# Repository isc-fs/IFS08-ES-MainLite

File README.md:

# IFS08-ES-MainLite

Hardware design, KiCad schematic and PCB layout of the **MainLite**, the minimal STM32H733ZG control module of the **IFS08**, developed for the **ISC Formula Student Racing Team** (Season 2025/2026). Mounted on a backplane, the same module becomes the **AMS**, the **ECU** or the **uDV**.

[-green.svg)]()
[-red.svg)]()

---

## Getting started

1. Create a GitHub account if you don't have one yet.
2. Download and install [GitHub Desktop](https://desktop.github.com/) (beginner) or [Git CLI](https://git-scm.com/book/en/v2/Getting-Started-Installing-Git) (advanced).
   - If this is your first time using GitHub Desktop, make sure to read the [User Manual](https://help.github.com/desktop/guides/).
   - If this is your first time using Git, start with a tutorial:
     - [Git Tutorial](https://git-scm.com/docs/gittutorial)
     - [Atlassian Git Tutorial](https://www.atlassian.com/git/tutorials/)
   - Keep a copy of [GitHub's Git Cheat Sheet](https://services.github.com/kit/downloads/github-git-cheat-sheet.pdf) handy as a reference.

3. Clone this repository to your machine:
   - **SSH:** `git@github.com:isc-fs/IFS08-ES-MainLite.git`
   - **HTTPS:** `https://github.com/isc-fs/IFS08-ES-MainLite.git`

4. Open `IFS08-MainLite/MAIN_LITE.kicad_pro` with KiCad 9.x.

---

## How we work with this repository

### Main branches

The repository follows standard ISC branching rules:

* **`main`** is the production branch. It contains only validated hardware releases, schematics, and documentation ready for track operations. Never work directly on it.
* **`dev`** (or active feature branches) is the development and integration point. Never commit directly to `main` — all changes arrive through a reviewed Pull Request.

```
main  ──────────────────●──────────────────────●──▶  (validated releases only)
                        ↑                      ↑
dev   ──────●───●───●───●───●───●───●───●───●──●──▶  (continuous integration)
            ↑   ↑       ↑   ↑   ↑       ↑   ↑
          feat/1 fix/1 feat/2 fix/2   feat/3 fix/3
```

### Feature branches

All work — whether a new hardware revision, firmware update, or bug fix — is done on a **feature branch** created from `dev` (or `main`). When the work is ready, a Pull Request is opened, reviewed, merged, and the branch is deleted.

```
feat/<n>   →  new functionality / hardware addition (feat/1, feat/2, feat/3 ...)
fix/<n>    →  bug fix / schematic correction       (fix/1,  fix/2,  fix/3  ...)
```

### Step-by-step workflow

1. **Create the branch:**
   ```bash
   git checkout dev
   git pull origin dev
   git checkout -b feat/your-feature-name
   ```
2. **Work and commit:**
   ```bash
   git add .
   git commit -m "feat(hw): add reverse polarity protection to 5V input"
   ```
3. **Push and open Pull Request:**
   ```bash
   git push origin feat/your-feature-name
   ```
   Open a PR against `dev`, verify 0 KiCad DRC/ERC errors, provide test evidence, and request review from the Electronics Subsystem Technical Director.

---

## 1. Project Overview & System Purpose

The **MainLite** is a small, self-contained STM32H733ZG module: MCU, 3.3 V regulation, three CAN transceivers, IMU, microSD, USB-C and SWD. Everything that changes between car subsystems lives on the **backplane** it plugs into through two 1×18 2.54 mm headers (**J3** and **J4**):

| Role | Node id (CAN bootloader) | Flash bus |
| :--- | :---: | :---: |
| **ECU** — vehicle control unit | `0x1` | FDCAN2 |
| **AMS** — accumulator management system | `0x2` | FDCAN1 |
| **uDV** — driverless interface | `0x3` | FDCAN2 |

Every MainLite carries the ISC CAN bootloader in flash sector 0.

```
                 +--------------------------------------------------------------+
   USB-C (J5) ---+  ESD (D3/D4)   +5V <- VBUS (D11)        SWD (J2: GND/CLK/DIO/VDD)
                 |                                                              |
   +5V (J4.17/18)+--> LD39200 (U1) --> VDD 3.3 V --> J4.15/16                   |
                 |                                                              |
                 |      +--------------------------------------------+         |
                 |      |        STM32H733ZGTx (U5, LQFP-144)         |         |
                 |      |  HSE 24 MHz (Y1)                            |         |
                 |      +--+---------+---------+---------+------+----+         |
                 |         |FDCAN1   |FDCAN2   |FDCAN3   |I2C2  |SDMMC1        |
                 |      TCAN330   TCAN330   TCAN330   BMI088  microSD (J1)      |
                 |       (U2)      (U3)      (U4)     (IC1)    4-bit, CD PE3    |
                 |      120R R1   120R R5   120R R9                             |
                 +--------+---------+---------+-----------------------------+---+
                          |         |         |                             |
                   J4.3/4 CAN1  J4.5/6 CAN2  J4.7/8 CAN3     J3: 13 GPIO, USART10, 1-Wire
                                                            J4: SPI1 + nRF24 CS/CE/IRQ
```

---

## 2. Hardware Architecture & Electrical Specifications

| Block | Part | Notes |
| :--- | :--- | :--- |
| MCU | STM32H733ZGTx (U5) | Cortex-M7 @ 550 MHz, 1 MB flash, LQFP-144 |
| Clock | 24 MHz crystal (Y1) | HSE on PH0/PH1, 10 pF load caps (C5/C6) |
| 3.3 V rail | ST LD39200PU33R (U1) | From `+5V` (backplane J4.17/18 or USB VBUS through D11) |
| CAN | 3× TI TCAN330 (U2/U3/U4) | FDCAN1 PD0/PD1, FDCAN2 PB12/PB13, FDCAN3 PG10/PG9; fixed 120 Ω terminations R1/R5/R9 |
| IMU | Bosch BMI088 (IC1) | I2C2 PF0/PF1, accel `0x18`, gyro `0x68`, no external pull-ups |
| Storage | microSD (J1, Molex 104031-0811) | SDMMC1 4-bit PC8–PC12/PD2, 33 Ω series, 47 kΩ pull-ups, card detect PE3 |
| USB | USB-C (J5, GCT USB4085) | USB_OTG_HS FS PHY PA11/PA12, VBUS sense PA9 (100k/47k) |
| Debug | 1×4 header (J2) | GND, SWCLK (PA14), SWDIO (PA13), VDD |
| Status | 2× LED | `OK_STATUS` PD14, `ERR_STATUS` PD15 |
| Buttons | SW1 / SW2 | BOOT0, NRST |
| VBAT | — | Not connected (no backup battery) |

---

## 3. Backplane Connectors (J3 / J4)

| Pin | J3 net | J3 MCU | J4 net | J4 MCU / part |
| :---: | :--- | :--- | :--- | :--- |
| 1 | `GND` | — | `GND` | — |
| 2 | `GND` | — | `GND` | — |
| 3 | `DS18B20_REFRI` | PD5 (pin 119) | `CANL1` | R1.2, U2.6 |
| 4 | `USART10_RX` | PG11 (pin 126) | `CANH1` | R1.1, U2.7 |
| 5 | `USART10_TX` | PG12 (pin 127) | `CANH2` | R5.1, U3.7 |
| 6 | `GPIO1` | PB4 (pin 134) | `CANL2` | R5.2, U3.6 |
| 7 | `GPIO2` | PB5 (pin 135) | `CANH3` | R9.1, U4.7 |
| 8 | `GPIO3` | PB6 (pin 136) | `CANL3` | R9.2, U4.6 |
| 9 | `GPIO4` | PB7 (pin 137) | `NRF24_CS` | PB0 (pin 46) |
| 10 | `GPIO5` | PB8 (pin 139) | `NRF24_CE` | PC5 (pin 45) |
| 11 | `GPIO6` | PB9 (pin 140) | `NRF24_IRQ` | PC4 (pin 44) |
| 12 | `GPIO7` | PF7 (pin 19) | `SPI1_MOSI` | PA7 (pin 43) |
| 13 | `GPIO8` | PF8 (pin 20) | `SPI1_MISO` | PA6 (pin 42) |
| 14 | `GPIO9` | PF9 (pin 21) | `SPI1_SCK` | PA5 (pin 41) |
| 15 | `GPIO10` | PF10 (pin 22) | `VDD` | — |
| 16 | `GPIO11` | PC0 (pin 26) | `VDD` | — |
| 17 | `GPIO12` | PC1 (pin 27) | `+5V` | — |
| 18 | `GPIO13` | PC2_C (pin 28) | `+5V` | — |

Per-role use of these pins (which GPIO is which signal on the AMS, ECU or uDV backplane) is defined by each backplane design.

---

## 4. Machine-Readable Pin Model

[`model/mainlite.pins.yaml`](model/mainlite.pins.yaml) (JSON twin: [`mainlite.pins.json`](model/mainlite.pins.json)) lists all 144 pins of U5: net, alternate function, whether and where each one leaves the module on J3/J4, and what it connects to on the board. It also describes the CAN, SDMMC, I2C, HSE, VBAT, SWD and USB interfaces. `tools/gen_pins.py` generates it from the schematic; CI fails a PR whose committed model is stale or whose schematic has KiCad ERC errors. Each change that reaches `main` is published as a `pin-model-vX.Y` release, so other repos (e.g. the virtual HIL) can check their pin definitions against a pinned version.

```bash
python3 tools/gen_pins.py        # after any schematic change; commit model/
```

Format, versioning and how to consume it: [docs/pin-model.md](docs/pin-model.md).

---

## 5. Formal Design Documents & Reports

| Document | File Link | Description | Status |
| :--- | :--- | :--- | :--- |
| **Work Order (PDF)** | [📄 WO_ES-IFS08-MainLite.pdf](WO_ES-IFS08-MainLite.pdf) | Formal Work Order (`WO-IFS08-MLITE-001`): requirements, interfaces, verification protocol and QA sign-off sheet. | **Rev 1.0** |
| **Work Order (DOCX)** | [📄 WO_ES-IFS08-MainLite.docx](WO_ES-IFS08-MainLite.docx) | Word source of the Work Order, on the ISC base template styles. | **Rev 1.0** |
| **Markdown Specification** | [📄 WORK_ORDER_MAIN_LITE.md](docs/WORK_ORDER_MAIN_LITE.md) | Synchronized Markdown version of the Work Order for Git version control and quick online reference. | **Rev 1.0** |
| **Schematic (PDF)** | [📄 MAIN_LITE_schematic.pdf](docs/MAIN_LITE_schematic.pdf) | Eeschema PDF export of the schematic. | **v1.1** |
| **Interactive BOM** | [📄 MAIN_LITE_v1-1_BOM.html](docs/bom/MAIN_LITE_v1-1_BOM.html) | InteractiveHtmlBom export for assembly. | **v1.1** |
| **Pin model** | [📄 pin-model.md](docs/pin-model.md) | Format and use of the generated pin model. | **Schema v1** |
| **Fabrication outputs** | [📁 production/](IFS08-MainLite/production) | Gerbers/drill (`MAIN_LITE.zip`), BOM, CPL and IPC netlist as sent to fab. | **v1.1** |

---

## 6. Repository Structure

```
IFS08-ES-MainLite/
├── .github/workflows/                 # CI: pin-model check + ERC, model release on main
├── docs/                              # Documentation
│   ├── bom/
│   │   └── MAIN_LITE_v1-1_BOM.html    # Interactive BOM
│   ├── MAIN_LITE_schematic.pdf        # Schematic PDF export
│   ├── pin-model.md                   # Pin model format & usage
│   └── WORK_ORDER_MAIN_LITE.md        # Synchronized Markdown Work Order
├── IFS08-MainLite/                    # KiCad Project Files (KiCad 9.x)
│   ├── Libraries/                     # Local symbols & footprints (BMI088, LD39200, LSM115J, switch, ISC logo, MainLite module)
│   ├── production/                    # Fabrication outputs (Gerbers, BOM, CPL)
│   ├── fp-lib-table                   # Footprint Library Table
│   ├── sym-lib-table                  # Symbol Library Table
│   ├── MAIN_LITE.kicad_pro            # KiCad Project File
│   ├── MAIN_LITE.kicad_sch            # Schematic
│   └── MAIN_LITE.kicad_pcb            # PCB Layout
├── model/                             # GENERATED pin model (mainlite.pins.yaml / .json)
├── tests/                             # Pin model invariants (unittest)
├── tools/                             # gen_pins.py, kicad_export.sh, erc_summary.py, ST pin data
├── WO_ES-IFS08-MainLite.pdf           # Official Work Order (PDF)
├── WO_ES-IFS08-MainLite.docx          # Official Work Order (Word)
├── .gitignore                         # KiCad and OS Ignore Rules
└── README.md                          # Repository Documentation
```

`Libraries/MAIN_LITE/` holds the MainLite module symbol and footprint that backplane designs place to mate with J3/J4.

---

## 7. Author & Team Credits

* **Subsystem:** Low Voltage & Electronics Subsystem (ES)
* **Author & Technical Lead:** Raúl Morán
* **Team:** [ISC Formula Student Racing Team](https://www.comillas.edu/) — Universidad Pontificia Comillas (ICAI)
* **Season:** 2025 / 2026

---

*ISC Racing Team — IFS08 Electronics Subsystem*

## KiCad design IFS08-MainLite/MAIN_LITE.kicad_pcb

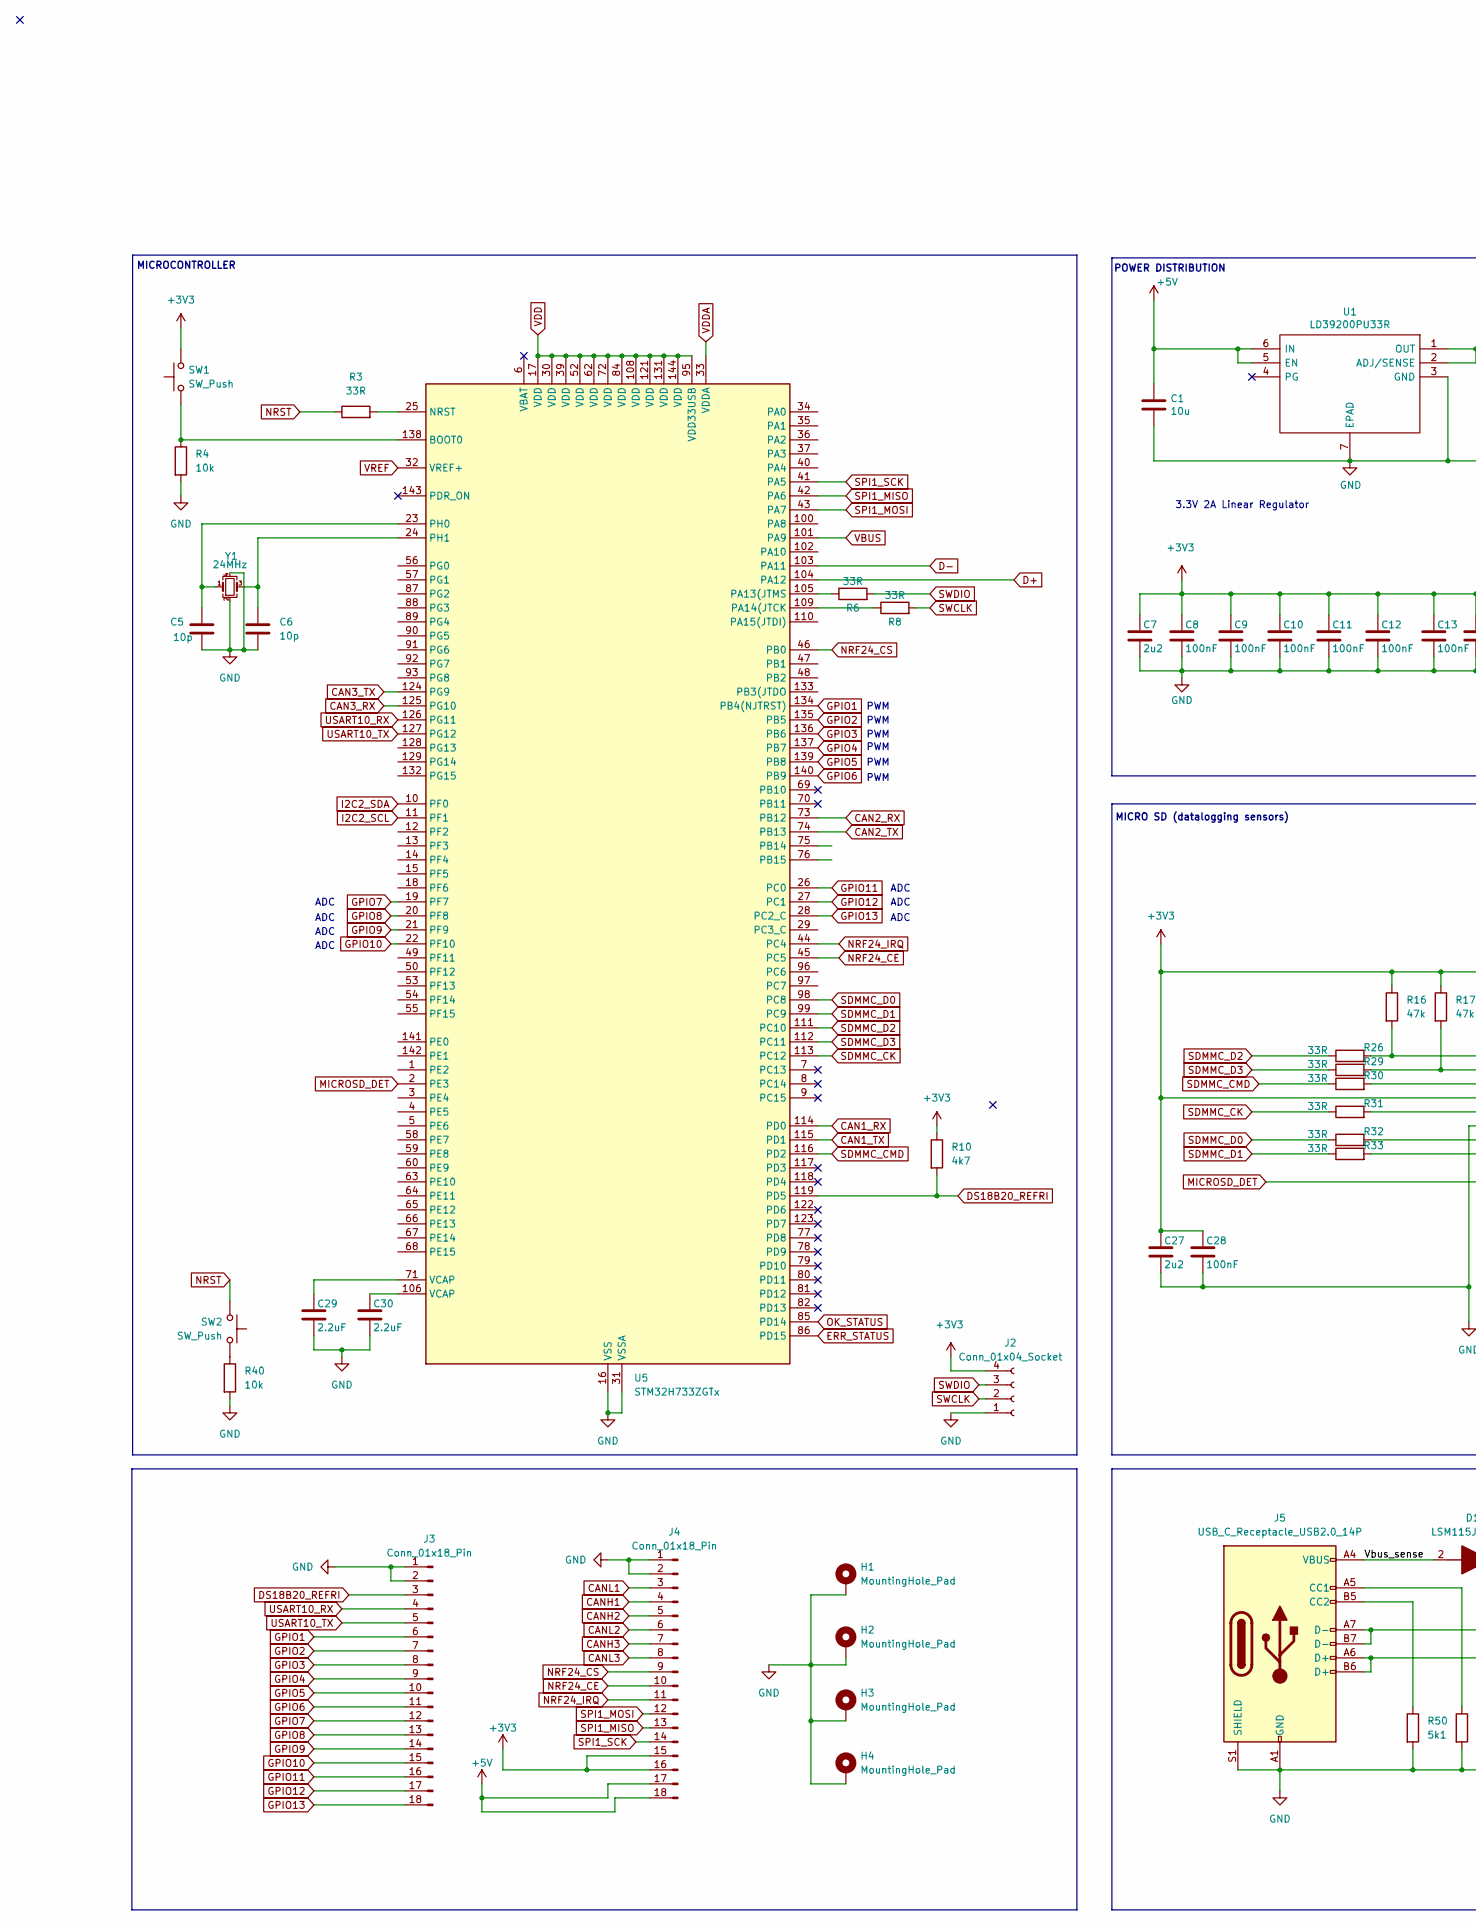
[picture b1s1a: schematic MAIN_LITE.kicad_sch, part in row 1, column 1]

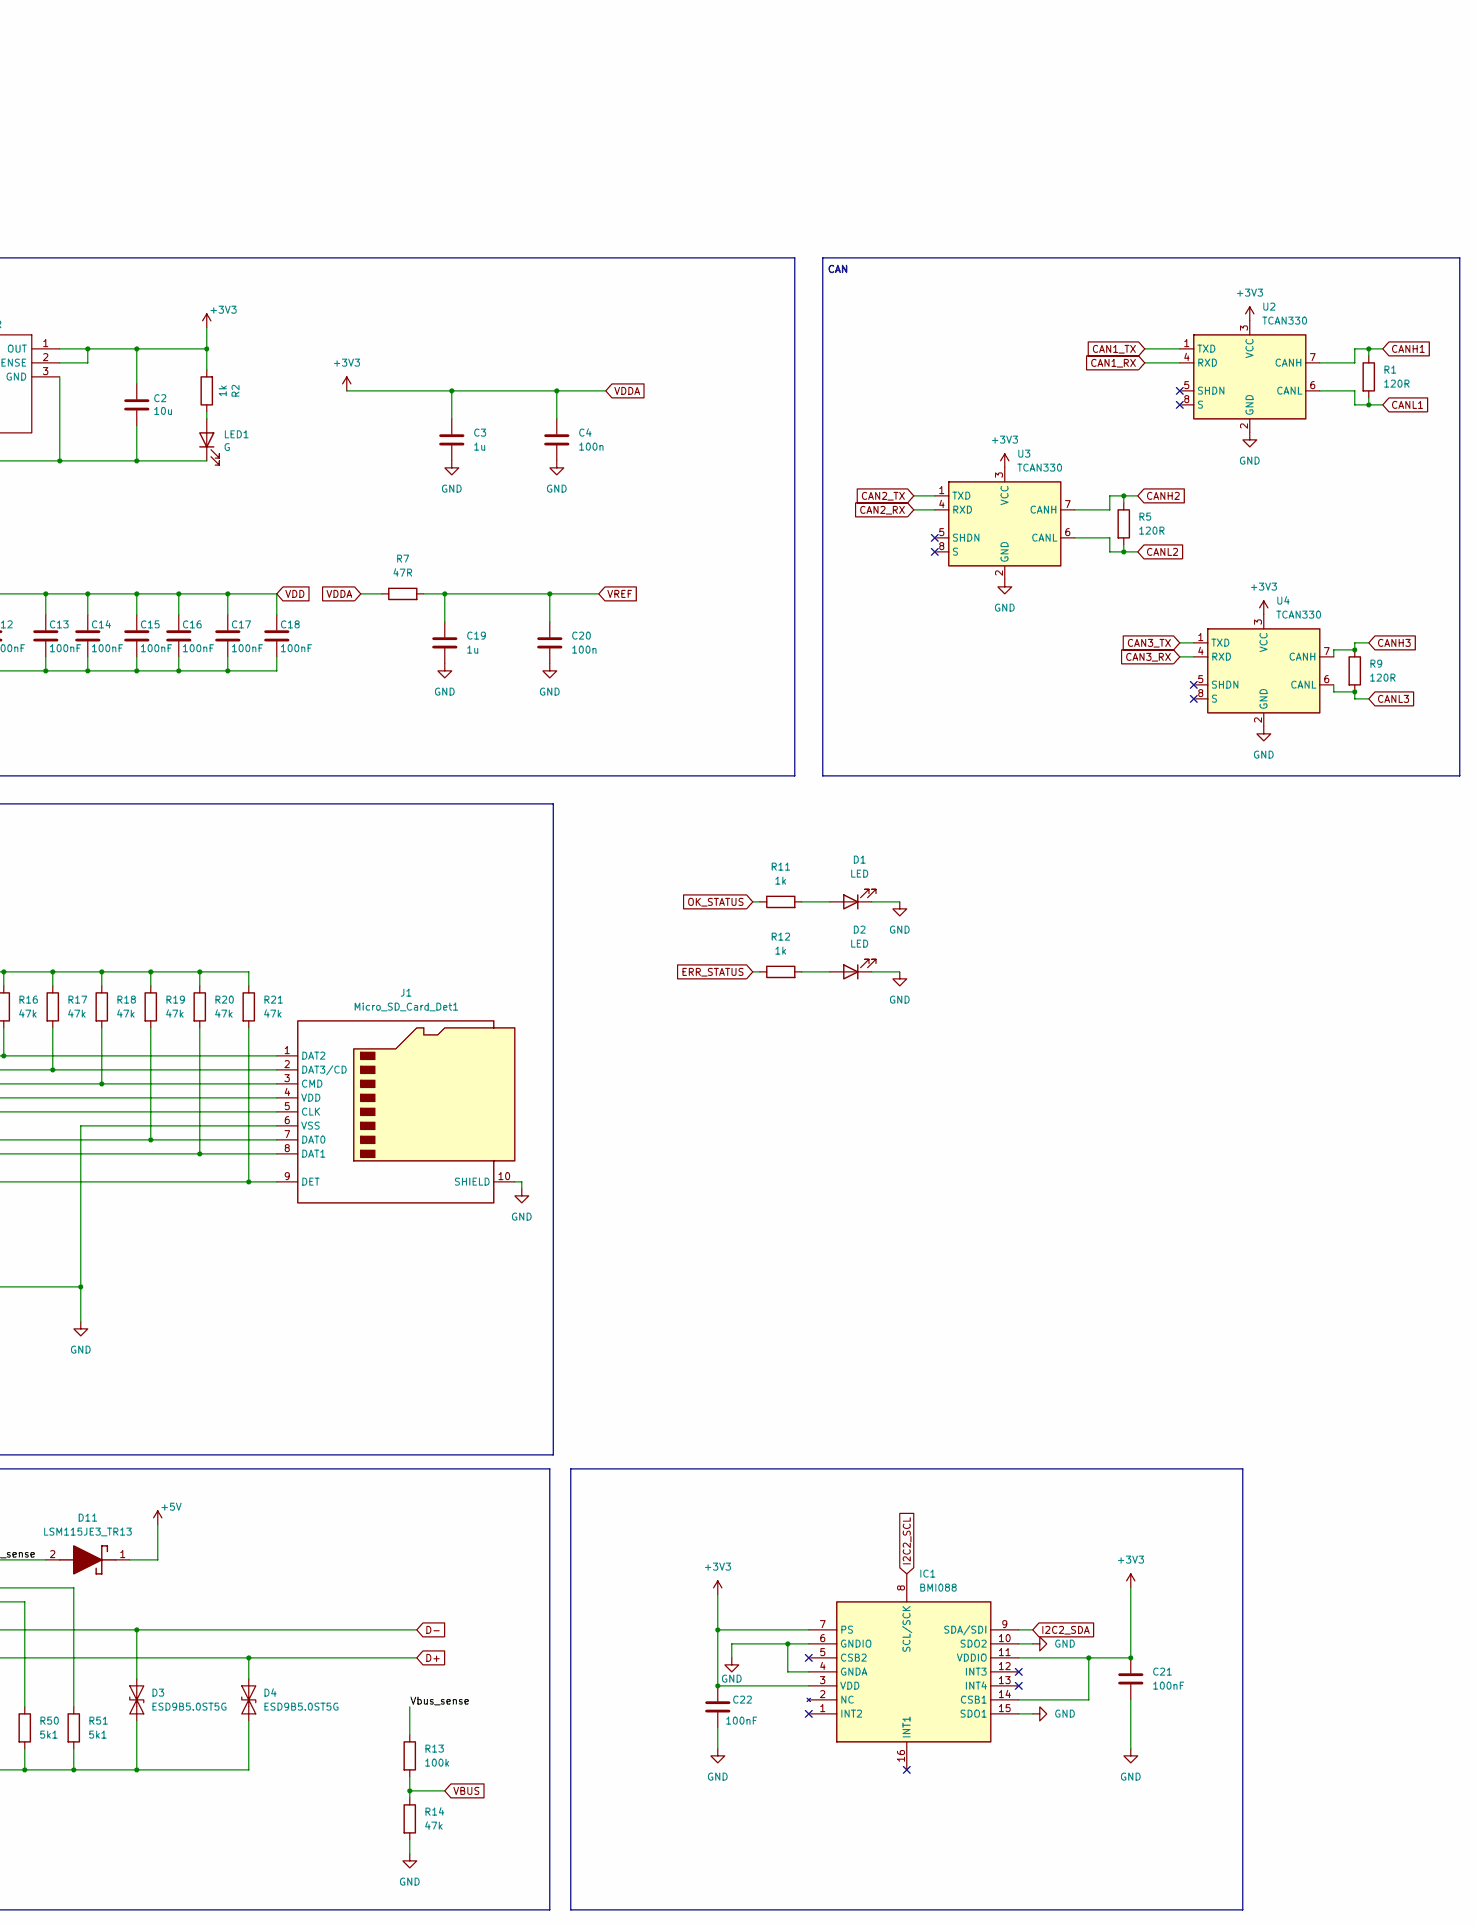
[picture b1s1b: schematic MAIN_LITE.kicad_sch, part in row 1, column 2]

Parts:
C1, C2: 10u; C_0603_1608Metric
C3, C19: 1u; C_0805_2012Metric_Pad1.18x1.45mm_HandSolder
C4, C20: 100n; C_0603_1608Metric_Pad1.08x0.95mm_HandSolder
C5, C6: 10p; C_0603_1608Metric_Pad1.08x0.95mm_HandSolder
C7, C27: 2u2; C_0603_1608Metric_Pad1.08x0.95mm_HandSolder
C8, C9, C10, C11, C12, C13, C14, C15, C16, C17, C18, C28: 100nF; C_0603_1608Metric_Pad1.08x0.95mm_HandSolder
C21, C22: 100nF; C_0402_1005Metric
C29, C30: 2.2uF; C_0805_2012Metric_Pad1.18x1.45mm_HandSolder
D1, D2: LED; LED_0805_2012Metric
D3, D4: ESD9B5.0ST5G; D_SOD-923
D11: LSM115JE3_TR13; DIOM5436X330N; Mouser Part Number 494-LSM115JE3/TR13
H1, H2, H3, H4: MountingHole_Pad; MountingHole_3.2mm_M3_DIN965_Pad
IC1: BMI088; Mouser Part Number 262-BMI088
J1: Micro_SD_Card_Det1; microSD_HC_Molex_104031-0811
J2: Conn_01x04_Socket; PinHeader_1x04_P2.54mm_Vertical
J3, J4: Conn_01x18_Pin; PinHeader_1x18_P2.54mm_Vertical
J5: USB_C_Receptacle_USB2.0_14P; USB_C_Receptacle_GCT_USB4085
LED1: G; LED_0805_2012Metric
R1, R5, R9: 120R; R_0805_2012Metric_Pad1.20x1.40mm_HandSolder
R2: 1k; R_0603_1608Metric
R3, R6, R8, R26, R29, R30, R31, R32, R33: 33R; R_0805_2012Metric_Pad1.20x1.40mm_HandSolder
R4, R40: 10k; R_0805_2012Metric_Pad1.20x1.40mm_HandSolder
R7: 47R; R_0805_2012Metric_Pad1.20x1.40mm_HandSolder
R10: 4k7; R_0603_1608Metric_Pad0.98x0.95mm_HandSolder
R11, R12: 1k; R_0603_1608Metric_Pad0.98x0.95mm_HandSolder
R13: 100k; R_0603_1608Metric_Pad0.98x0.95mm_HandSolder
R14, R16, R17, R18, R19, R20, R21: 47k; R_0603_1608Metric_Pad0.98x0.95mm_HandSolder
R50, R51: 5k1; R_0603_1608Metric_Pad0.98x0.95mm_HandSolder
SW1, SW2: SW_Push; SW_SPST_B3U-1000P-B
U1: LD39200PU33R; SON95P300X300X100-7N-D; Manufacturer_Part_Number LD39200PU33R; Mouser Part Number 511-LD39200PU33R
U2, U3, U4: TCAN330; SOIC-8_3.9x4.9mm_P1.27mm
U5: STM32H733ZGTx; LQFP-144_20x20mm_P0.5mm
Y1: 24MHz; Crystal_SMD_2520-4Pin_2.5x2.0mm

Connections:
+5V: C1.1, D11.1 (K), J4.17, J4.18, U1.5 (EN), U1.6 (IN)
/Vbus_sense: D11.2 (A), J5.A4 (VBUS), J5.A9 (VBUS), J5.B4 (VBUS), J5.B9 (VBUS), R13.1
CAN1_RX: U2.4 (RXD), U5.114 (PD0)
CAN1_TX: U2.1 (TXD), U5.115 (PD1)
CAN2_RX: U3.4 (RXD), U5.73 (PB12)
CAN2_TX: U3.1 (TXD), U5.74 (PB13)
CAN3_RX: U4.4 (RXD), U5.125 (PG10)
CAN3_TX: U4.1 (TXD), U5.124 (PG9)
CANH1: J4.4, R1.1, U2.7 (CANH)
CANH2: J4.5, R5.1, U3.7 (CANH)
CANH3: J4.7, R9.1, U4.7 (CANH)
CANL1: J4.3, R1.2, U2.6 (CANL)
CANL2: J4.6, R5.2, U3.6 (CANL)
CANL3: J4.8, R9.2, U4.6 (CANL)
D+: D4.2 (A2), J5.A6 (D+), J5.B6 (D+), U5.104 (PA12)
D-: D3.2 (A2), J5.A7 (D-), J5.B7 (D-), U5.103 (PA11)
DS18B20_REFRI: J3.3, R10.2, U5.119 (PD5)
ERR_STATUS: R12.1, U5.86 (PD15)
GND: C1.2, C2.2, C3.1, C4.1, C5.2, C6.2, C7.2, C8.2, C9.2, C10.2, C11.2, C12.2, C13.2, C14.2, C15.2, C16.2, C17.2, C18.2, C19.1, C20.1, C21.2, C22.2, C27.2, C28.2, C29.2, C30.2, D1.1 (K), D2.1 (K), D3.1 (A1), D4.1 (A1), H1.1, H2.1, H3.1, H4.1, IC1.4 (GNDA), IC1.6 (GNDIO), IC1.10 (SDO2), IC1.15 (SDO1), J1.6 (VSS), J1.10 (SHIELD), J2.1, J3.1, J3.2, J4.1, J4.2, J5.A1 (GND), J5.A12 (GND), J5.B1 (GND), J5.B12 (GND), J5.S1 (SHIELD), LED1.1 (K), R4.2, R14.2, R40.2, R50.2, R51.2, U1.3 (GND), U1.7 (EPAD), U2.2 (GND), U3.2 (GND), U4.2 (GND), U5.16 (VSS), U5.31 (VSSA), U5.38 (VSS), U5.51 (VSS), U5.61 (VSS), U5.83 (VSS), U5.94 (VSS), U5.107 (VSS), U5.120 (VSS), U5.130 (VSS), Y1.2, Y1.4
GPIO1: J3.6, U5.134 (PB4(NJTRST))
GPIO2: J3.7, U5.135 (PB5)
GPIO3: J3.8, U5.136 (PB6)
GPIO4: J3.9, U5.137 (PB7)
GPIO5: J3.10, U5.139 (PB8)
GPIO6: J3.11, U5.140 (PB9)
GPIO7: J3.12, U5.19 (PF7)
GPIO8: J3.13, U5.20 (PF8)
GPIO9: J3.14, U5.21 (PF9)
GPIO10: J3.15, U5.22 (PF10)
GPIO11: J3.16, U5.26 (PC0)
GPIO12: J3.17, U5.27 (PC1)
GPIO13: J3.18, U5.28 (PC2_C)
I2C2_SCL: IC1.8 (SCL/SCK), U5.11 (PF1)
I2C2_SDA: IC1.9 (SDA/SDI), U5.10 (PF0)
MICROSD_DET: J1.9 (DET), R21.2, U5.2 (PE3)
NRF24_CE: J4.10, U5.45 (PC5)
NRF24_CS: J4.9, U5.46 (PB0)
NRF24_IRQ: J4.11, U5.44 (PC4)
NRST: R3.1, SW2.2
unnamed: C29.1, U5.71 (VCAP)
unnamed: C30.1, U5.106 (VCAP)
unnamed: D1.2 (A), R11.2
unnamed: D2.2 (A), R12.2
unnamed: J1.5 (CLK), R31.2
unnamed: J1.3 (CMD), R18.2, R30.2
unnamed: J1.7 (DAT0), R19.2, R32.2
unnamed: J1.8 (DAT1), R20.2, R33.2
unnamed: J1.1 (DAT2), R16.2, R26.2
unnamed: J1.2 (DAT3/CD), R17.2, R29.2
unnamed: J5.A5 (CC1), R51.1
unnamed: J5.B5 (CC2), R50.1
unnamed: LED1.2 (A), R2.1
unnamed: R40.1, SW2.1
unnamed: R4.1, SW1.1, U5.138 (BOOT0)
unnamed: R3.2, U5.25 (NRST)
unnamed: R6.1, U5.105 (PA13(JTMS)
unnamed: R8.1, U5.109 (PA14(JTCK)
unnamed: C5.1, U5.23 (PH0), Y1.1
unnamed: C6.1, U5.24 (PH1), Y1.3
OK_STATUS: R11.1, U5.85 (PD14)
SDMMC_CK: R31.1, U5.113 (PC12)
SDMMC_CMD: R30.1, U5.116 (PD2)
SDMMC_D0: R32.1, U5.98 (PC8)
SDMMC_D1: R33.1, U5.99 (PC9)
SDMMC_D2: R26.1, U5.111 (PC10)
SDMMC_D3: R29.1, U5.112 (PC11)
SPI1_MISO: J4.13, U5.42 (PA6)
SPI1_MOSI: J4.12, U5.43 (PA7)
SPI1_SCK: J4.14, U5.41 (PA5)
SWCLK: J2.2, R8.2
SWDIO: J2.3, R6.2
USART10_RX: J3.4, U5.126 (PG11)
USART10_TX: J3.5, U5.127 (PG12)
VBUS: R13.2, R14.1, U5.101 (PA9)
VDD: C2.1, C3.2, C4.2, C7.1, C8.1, C9.1, C10.1, C11.1, C12.1, C13.1, C14.1, C15.1, C16.1, C17.1, C18.1, C21.1, C22.1, C27.1, C28.1, IC1.3 (VDD), IC1.7 (PS), IC1.11 (VDDIO), IC1.14 (CSB1), J1.4 (VDD), J2.4, J4.15, J4.16, R2.2, R7.1, R10.1, R16.1, R17.1, R18.1, R19.1, R20.1, R21.1, SW1.2, U1.1 (OUT), U1.2 (ADJ/SENSE), U2.3 (VCC), U3.3 (VCC), U4.3 (VCC), U5.17 (VDD), U5.30 (VDD), U5.33 (VDDA), U5.39 (VDD), U5.52 (VDD), U5.62 (VDD), U5.72 (VDD), U5.84 (VDD), U5.95 (VDD33USB), U5.108 (VDD), U5.121 (VDD), U5.131 (VDD), U5.144 (VDD)
VREF: C19.2, C20.2, R7.2, U5.32 (VREF+)

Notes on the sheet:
ADC
PWM
MICRO SD (datalogging sensors)
3.3V 2A Linear Regulator
CAN
MICROCONTROLLER
POWER DISTRIBUTION

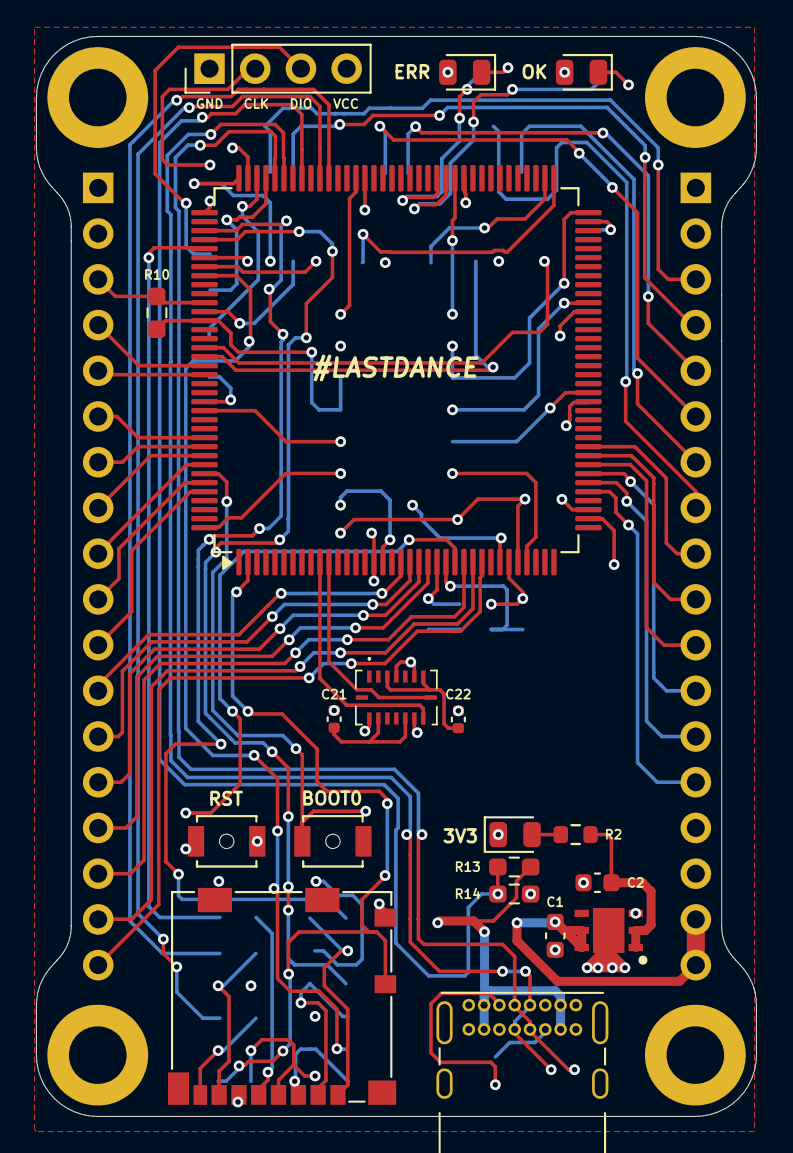
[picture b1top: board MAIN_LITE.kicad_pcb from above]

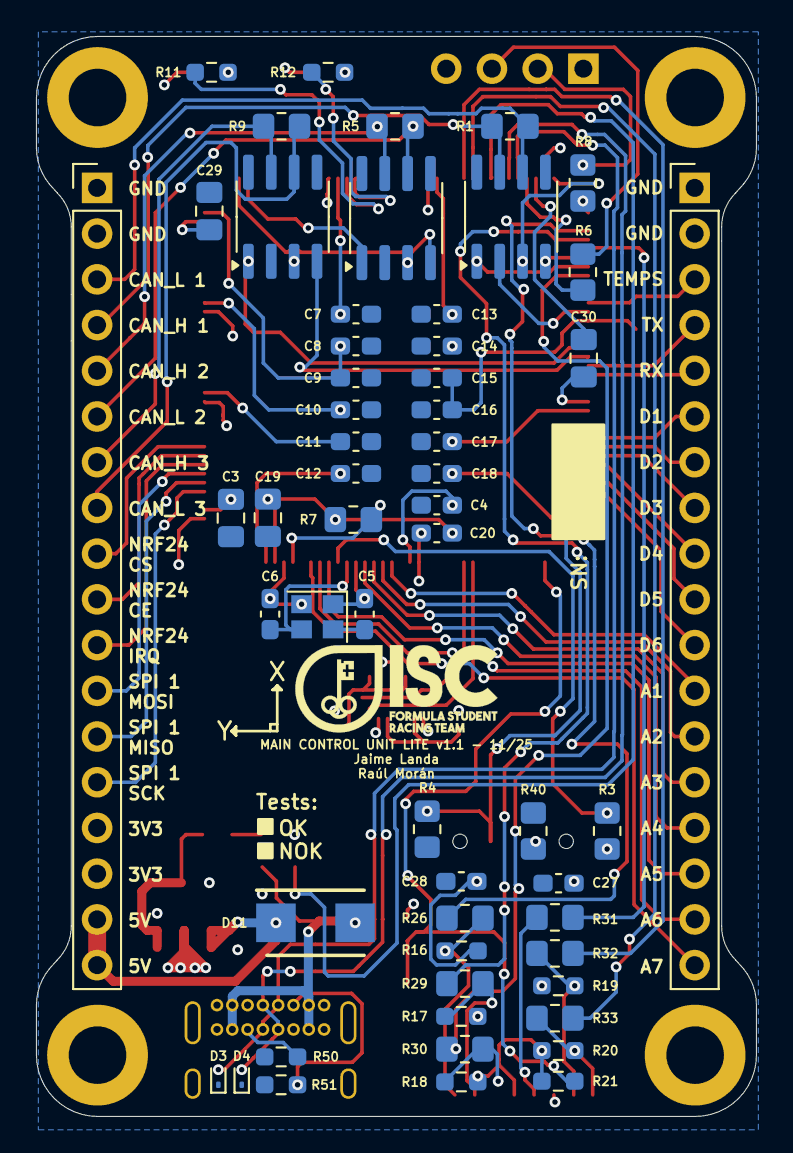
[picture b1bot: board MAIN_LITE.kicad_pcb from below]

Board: 2 copper layers, 40.0 x 60.0 mm, 80 parts (57 on the bottom side), 76 nets.

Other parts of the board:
G3: LOGO; LogoISC

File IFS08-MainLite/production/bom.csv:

Designator,Footprint,Quantity,Value,LCSC Part #
"C1, C2",0603,2,10u,
"C10, C11, C12, C13, C14, C15, C16, C17, C18, C28, C8, C9",0603,12,100nF,
"C19, C3",0805,2,1u,
"C20, C4",0603,2,100n,
"C21, C22",0402,2,100nF,
"C27, C7",0603,2,2u2,
"C29, C30",0805,2,2.2uF,
"C5, C6",0603,2,10p,
"D1, D2",0805,2,LED,
D11,DIOM5436X330N,1,LSM115JE3_TR13,
"D3, D4",D_SOD-923,2,ESD9B5.0ST5G,
G3,LogoISC,1,LOGO,
IC1,BMI088,1,BMI088,
J1,microSD_HC_Molex_104031-0811,1,Micro_SD_Card_Det1,
J2,PinHeader_1x04_P2.54mm_Vertical,1,Conn_01x04_Socket,
"J3, J4",PinHeader_1x18_P2.54mm_Vertical,2,Conn_01x18_Pin,
J5,USB_C_Receptacle_GCT_USB4085,1,USB_C_Receptacle_USB2.0_14P,
LED1,0805,1,G,
"R1, R5, R9",0805,3,120R,
R10,0603,1,4k7,
"R11, R12, R2",0603,3,1k,
R13,0603,1,100k,
"R14, R16, R17, R18, R19, R20, R21",0603,7,47k,
"R26, R29, R3, R30, R31, R32, R33, R6, R8",0805,9,33R,
"R4, R40",0805,2,10k,
"R50, R51",0603,2,5k1,
R7,0805,1,47R,
"SW1, SW2",SW_SPST_B3U-1000P-B,2,SW_Push,
U1,SON95P300X300X100-7N-D,1,LD39200PU33R,
"U2, U3, U4",SOIC-8_3.9x4.9mm_P1.27mm,3,TCAN330,
U5,LQFP-144_20x20mm_P0.5mm,1,STM32H733ZGTx,
Y1,Crystal_SMD_2520-4Pin_2.5x2.0mm,1,24MHz,
